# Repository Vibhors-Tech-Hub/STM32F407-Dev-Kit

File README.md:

# Tiny, yet powerful

The PCB for this project is just **66*59.5mm**, which is not exactly tiny, but still has features that go beyond it's  size. It packs a STM32F407, debugger (STM32F103), Ethernet, a powerful motor driver, 24-bit ADC configured for a 4 - wire Kelvin load, DAC and mic into this tiny footprint.

# Why did I build this?

I had designed general dev boards for the ESP32, or the RP2040, but never worked with the STM32 family before. And I also wanted to make a really complex PCB to brush up my skills, so I decided on this.

# Double-sided component placement

While I was designing this PCB, I realised that in real-life applications, size is a key deciding factor; something I had never taken very seriously. So, I challenged to make this board under 70*70mm this time. Due to which, I had to place **components on both sides**. Not only does it make the PCB smaller, but also improves SI and clears up board space.

# 4-layer design

A 2-layer design was clearly not an option here. I both analog and digital circuitry here, requiring clear return paths. So, I decided on a 4 layer board with a GND and power plane. The power plane is sectioned into 12V and 3V3 volts. I did this because while most of the PCB needed 3.3V, the motor driver required +12V with minimal voltage drops and maximum current. But when only a few tracks were left, I couldn't find space on the outer two signal layers. I only had two options from there; either upgrade to a 6 layer board (expensive and really time consuming), or use a power plane for a few signals. I thought it might ruin the return paths for sensitive signals, so I googled for guides on that topic. After going through the ["Should You Route Signals in Your PCB Power Plane?" by Altium Academy](https://resources.altium.com/p/should-you-route-signals-your-pcb-power-plane), I decided to use the Vcc power plane for routing leftover signals.

# GPIO headers

To keep the form factor of the PCB low and keep things organised, I didn't breakout GPIO headers. Although this limits the capabilities of the controller to the existing peripherals only, I still went with it as the whole idea of this project was to design a compact, complex PCB for learning new things. To expand the functionality a bit, I exposed two headers for UART and CAN.
# Motor drivers

In the beginning, I planned on two motor drivers, as in the Block Diagram and Power budget. But while designing the schematic, I thought that a single driver was enough and didn't design the second. But to keep things upgradeable, I still kept it in the Power budget and block diagram

# Power Supply

The board requires **+12v, +3V3 and +1V8** to work. For that, I use a 3-pin 10A TBC for inputting 12V, and regulating it down to +3V3 and +1V8. As calculated in the power budget, I need a power supply capable of delivering roughly 10A, though with the second motor removed, a 7.5A supply may also be used.

# How to use it?

1) Solder your PCB
2) Use an **ST-Link debugger (recommended)/USB to UARTconverter** to flash the [**DAPLink firmware by ARMbed**](https://github.com/ARMmbed/DAPLink) onto the STM32F103
3) Plug it in, and you're ready to go!

# Block Diagram

# PCB

# 3D view (front)

# 3D view (back)

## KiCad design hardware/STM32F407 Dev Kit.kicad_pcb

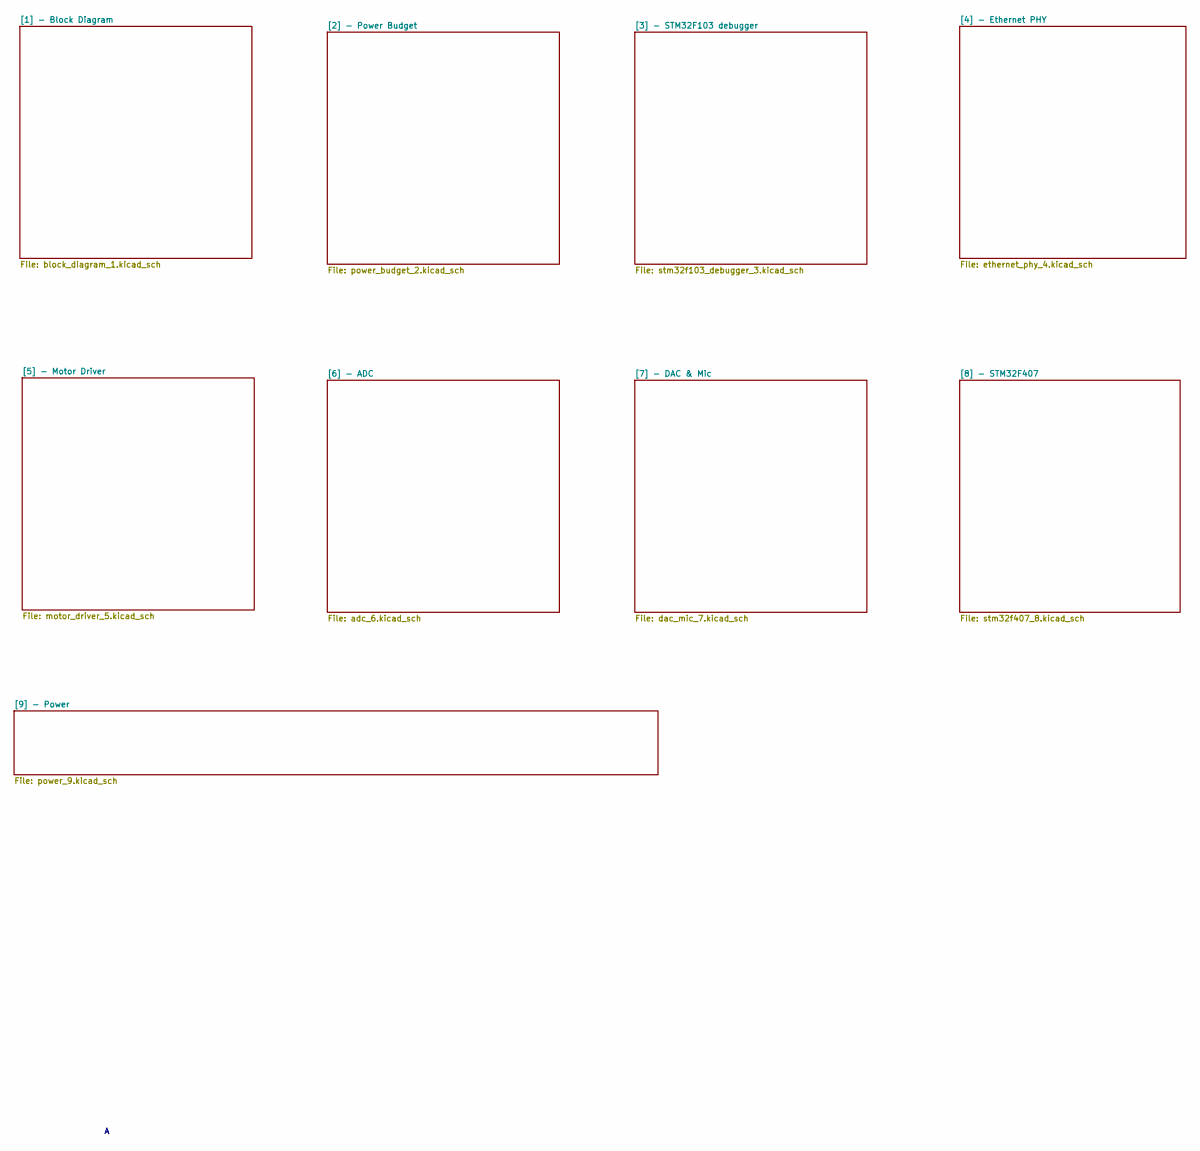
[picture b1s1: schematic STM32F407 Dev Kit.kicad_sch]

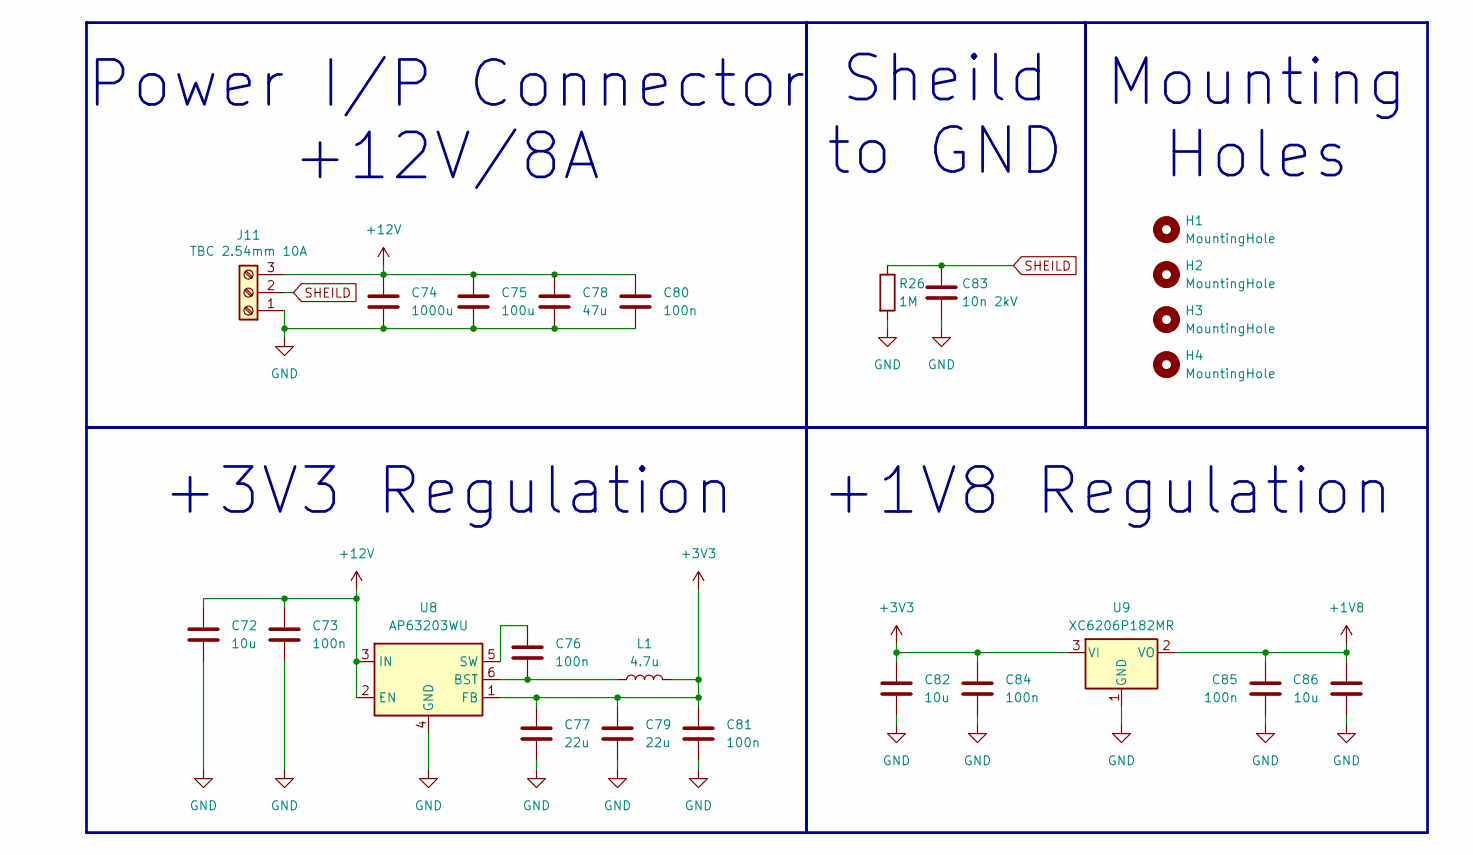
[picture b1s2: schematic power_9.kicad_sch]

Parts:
C72, C82, C86: 10u; C_0805_2012Metric_Pad1.18x1.45mm_HandSolder
C73, C76, C80, C81, C84, C85: 100n; C_0805_2012Metric_Pad1.18x1.45mm_HandSolder
C74: 1000u; CP_Elec_10x12.5
C75: 100u; C_1210_3225Metric_Pad1.33x2.70mm_HandSolder
C77, C79: 22u; C_0805_2012Metric_Pad1.18x1.45mm_HandSolder
C78: 47u; C_0805_2012Metric_Pad1.18x1.45mm_HandSolder
C83: 10n 2kV; C_1812_4532Metric_Pad1.57x3.40mm_HandSolder
H1, H2, H3, H4: MountingHole; MountingHole_3.5mm
J11: TBC 2.54mm 10A; TerminalBlock_Xinya_XY308-2.54-3P_1x03_P2.54mm_Horizontal
L1: 4.7u; L_0805_2012Metric_Pad1.05x1.20mm_HandSolder
R26: 1M; R_0805_2012Metric_Pad1.20x1.40mm_HandSolder
U8: AP63203WU; TSOT-23-6_HandSoldering
U9: XC6206P182MR; SOT-23-3

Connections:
+1V8: C85.1, C86.1, U9.2 (VO); also elsewhere on the board
+3V3: C77.1, C79.1, C81.1, C82.1, C84.1, L1.2, U8.1 (FB), U9.3 (VI); also elsewhere on the board
+12V: C72.1, C73.1, C74.1, C75.1, C78.1, C80.1, J11.3, U8.2 (EN), U8.3 (IN); also elsewhere on the board
GND: C72.2, C73.2, C74.2, C75.2, C77.2, C78.2, C79.2, C80.2, C81.2, C82.2, C83.2, C84.2, C85.2, C86.2, J11.1, R26.2, U8.4 (GND), U9.1 (GND); also elsewhere on the board
unnamed: C76.2, L1.1, U8.6 (BST)
unnamed: C76.1, U8.5 (SW)
SHEILD: C83.1, J11.2, R26.1; also elsewhere on the board

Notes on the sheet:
+3V3 Regulation
Sheild to GND
Power I/P Connector +12V/8A
Mounting Holes
+1V8 Regulation

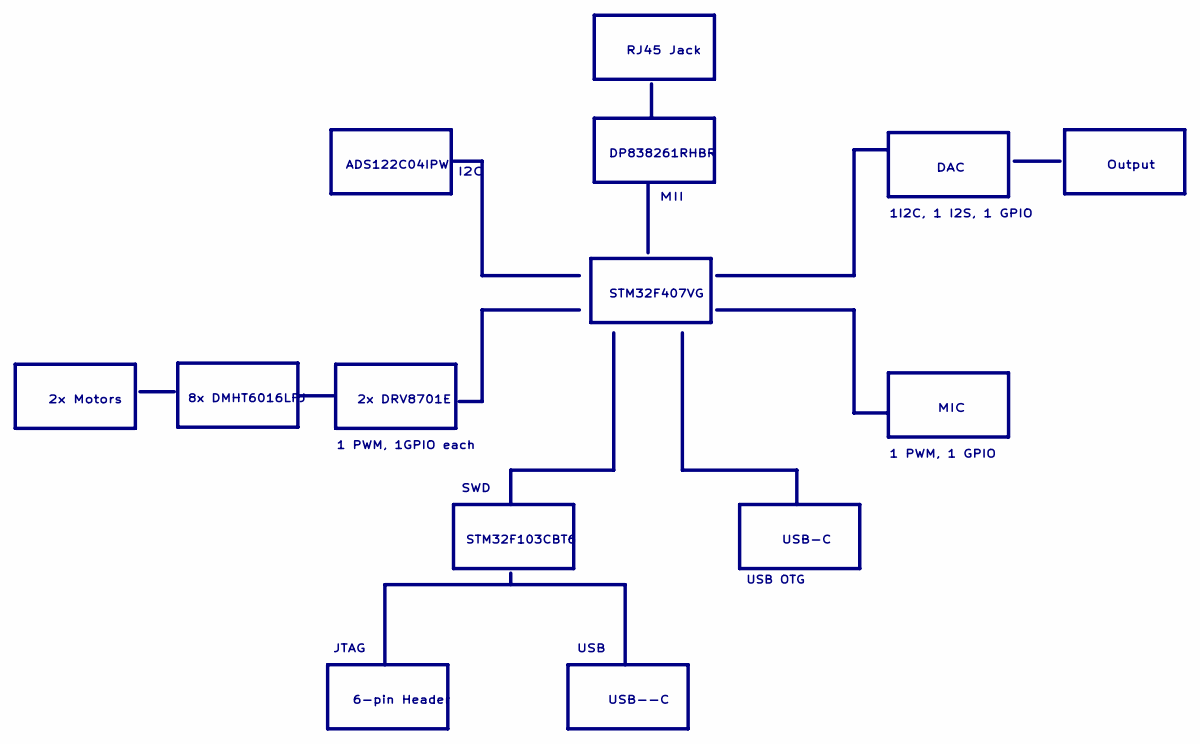
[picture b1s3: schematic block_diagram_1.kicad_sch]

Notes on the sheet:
6-pin Header
JTAG
DP838261RHBR
ADS122C04IPW
USB--C
2x Motors
USB-C
STM32F103CBT6
1 PWM, 1GPIO each
8x DMHT6016LFJ
STM32F407VG
SWD
Output
MIC
DAC
2x DRV8701E
RJ45 Jack
I2C
1I2C, 1 I2S, 1 GPIO
1 PWM, 1 GPIO
MII
USB
USB OTG

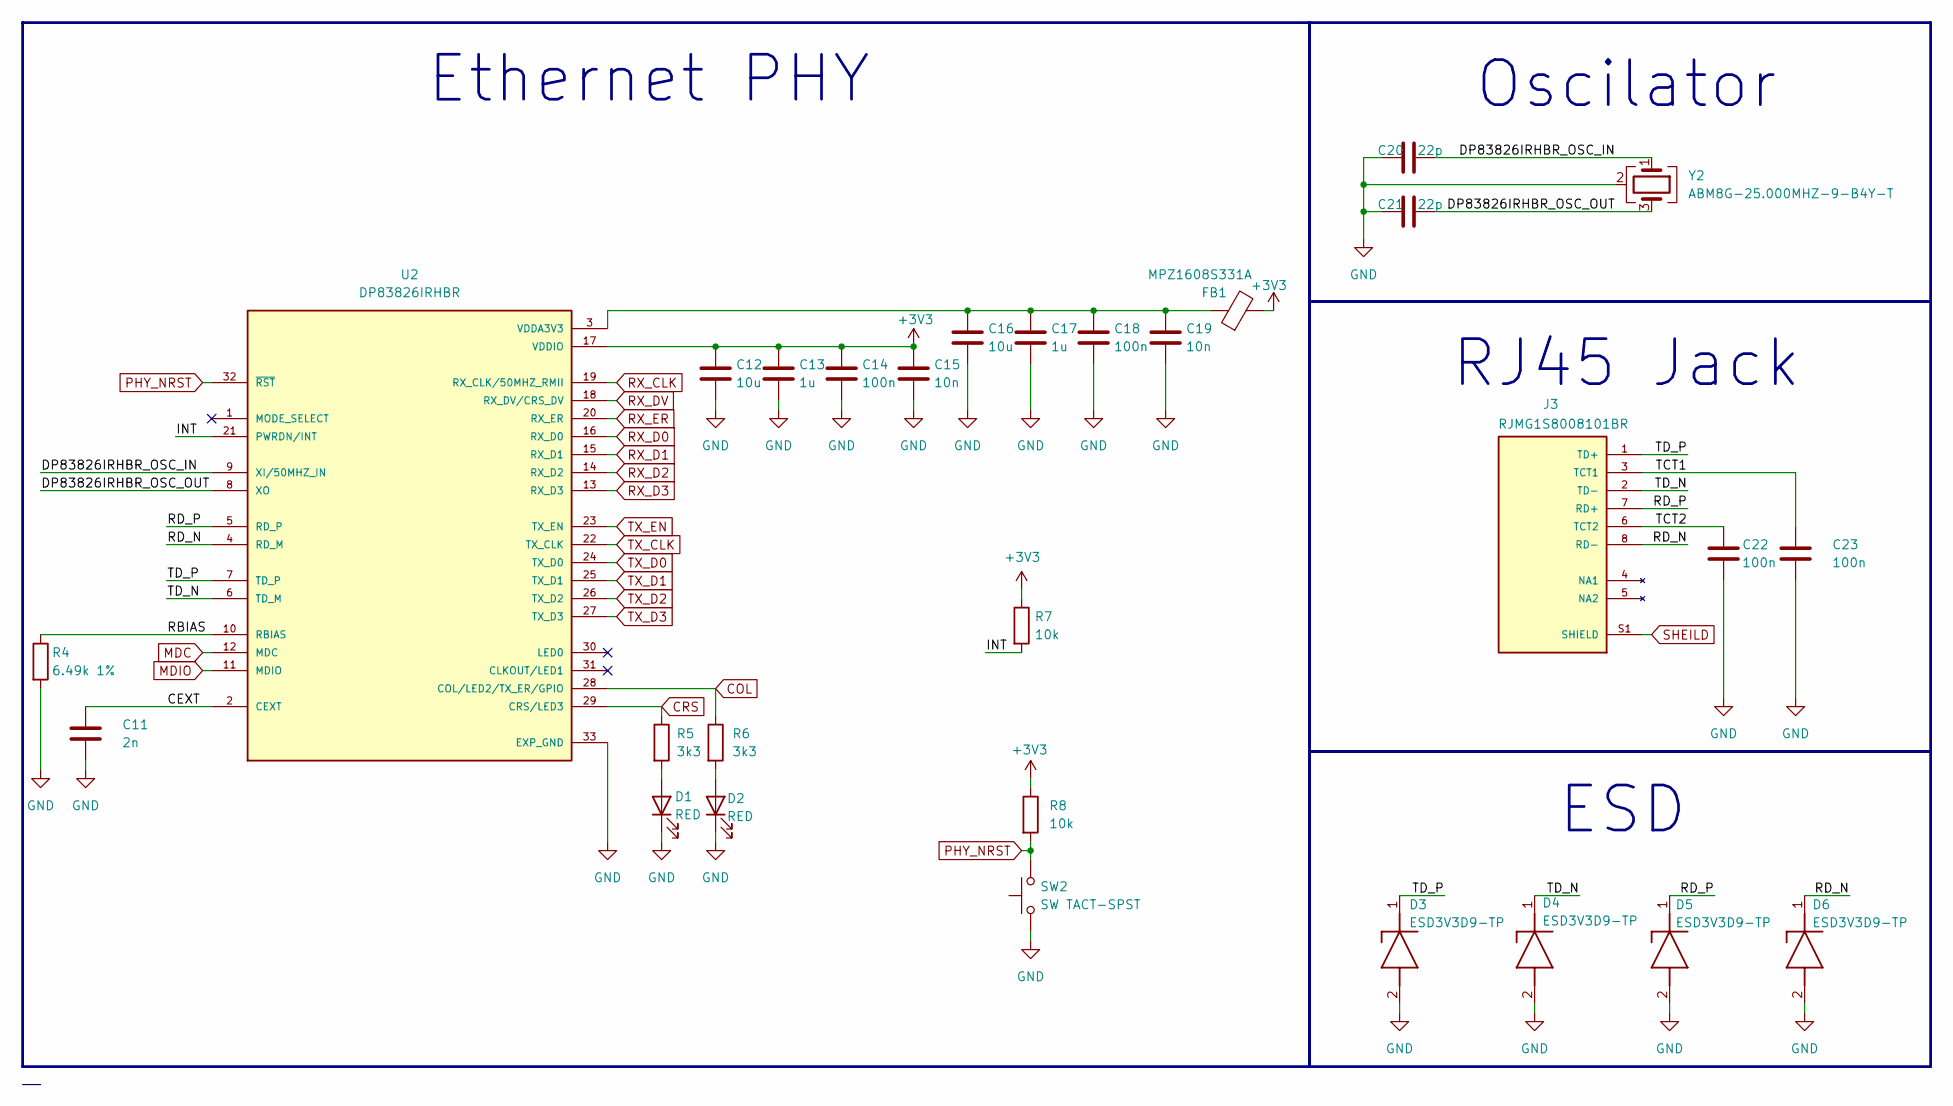
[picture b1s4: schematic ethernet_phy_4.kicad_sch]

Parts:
C11: 2n; C_0805_2012Metric_Pad1.18x1.45mm_HandSolder
C12, C16: 10u; C_0805_2012Metric_Pad1.18x1.45mm_HandSolder
C13, C17: 1u; C_0805_2012Metric_Pad1.18x1.45mm_HandSolder
C14, C18, C22, C23: 100n; C_0805_2012Metric_Pad1.18x1.45mm_HandSolder
C15, C19: 10n; C_0805_2012Metric_Pad1.18x1.45mm_HandSolder
C20, C21: 22p; C_0805_2012Metric_Pad1.18x1.45mm_HandSolder
D1, D2: RED; LED_0805_2012Metric_Pad1.15x1.40mm_HandSolder
D3, D4, D5, D6: ESD3V3D9-TP; D_SOD-923; Manufacturer_Part_Number ESD3V3D9-TP; Mouser Part Number 833-ESD3V3D9-TP
FB1: MPZ1608S331A; C_0603_1608Metric_Pad1.08x0.95mm_HandSolder
J3: RJMG1S8008101BR; PARTREV A
R4: 6.49k 1%; R_0805_2012Metric_Pad1.20x1.40mm_HandSolder
R5, R6: 3k3; R_0805_2012Metric_Pad1.20x1.40mm_HandSolder
R7, R8: 10k; R_0805_2012Metric_Pad1.20x1.40mm_HandSolder
SW2: SW TACT-SPST; SW_Push_SPST_NO_Alps_SKRK
U2: DP83826IRHBR; PARTREV G
Y2: ABM8G-25.000MHZ-9-B4Y-T; Crystal_SMD_3225-4Pin_3.2x2.5mm_HandSoldering

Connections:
+3V3: C12.1, C13.1, C14.1, C15.1, FB1.2, R7.1, R8.1, U2.17 (VDDIO); also elsewhere on the board
/[4] - Ethernet PHY/CEXT: C11.1, U2.2 (CEXT)
/[4] - Ethernet PHY/DP83826IRHBR_OSC_IN: C20.2, U2.9 (XI/50MHZ_IN), Y2.1
/[4] - Ethernet PHY/DP83826IRHBR_OSC_OUT: C21.2, U2.8 (XO), Y2.3
/[4] - Ethernet PHY/INT: R7.2, U2.21 (PWRDN/INT)
/[4] - Ethernet PHY/RBIAS: R4.1, U2.10 (RBIAS)
/[4] - Ethernet PHY/RD_N: D6.1 (K), J3.8 (RD-), U2.4 (RD_M)
/[4] - Ethernet PHY/RD_P: D5.1 (K), J3.7 (RD+), U2.5 (RD_P)
/[4] - Ethernet PHY/TCT1: C23.1, J3.3 (TCT1)
/[4] - Ethernet PHY/TCT2: C22.1, J3.6 (TCT2)
/[4] - Ethernet PHY/TD_N: D4.1 (K), J3.2 (TD-), U2.6 (TD_M)
/[4] - Ethernet PHY/TD_P: D3.1 (K), J3.1 (TD+), U2.7 (TD_P)
COL: R6.1, U2.28 (COL/LED2/TX_ER/GPIO); also elsewhere on the board
CRS: R5.1, U2.29 (CRS/LED3); also elsewhere on the board
GND: C11.2, C12.2, C13.2, C14.2, C15.2, C16.2, C17.2, C18.2, C19.2, C20.1, C21.1, C22.2, C23.2, D1.1 (K), D2.1 (K), D3.2 (A), D4.2 (A), D5.2 (A), D6.2 (A), R4.2, SW2.1, U2.33 (EXP_GND), Y2.2 (G), Y2.4 (G); also elsewhere on the board
MDC: U2.12 (MDC); also elsewhere on the board
MDIO: U2.11 (MDIO); also elsewhere on the board
unnamed: D1.2 (A), R5.2
unnamed: D2.2 (A), R6.2
unnamed: C16.1, C17.1, C18.1, C19.1, FB1.1, U2.3 (VDDA3V3)
PHY_NRST: R8.2, SW2.2, U2.32 (~RST); also elsewhere on the board
RX_CLK: U2.19 (RX_CLK/50MHZ_RMII); also elsewhere on the board
RX_D0: U2.16 (RX_D0); also elsewhere on the board
RX_D1: U2.15 (RX_D1); also elsewhere on the board
RX_D2: U2.14 (RX_D2); also elsewhere on the board
RX_D3: U2.13 (RX_D3); also elsewhere on the board
RX_DV: U2.18 (RX_DV/CRS_DV); also elsewhere on the board
RX_ER: U2.20 (RX_ER); also elsewhere on the board
SHEILD: J3.S1 (SHIELD), J3.S2 (SHIELD); also elsewhere on the board
TX_CLK: U2.22 (TX_CLK); also elsewhere on the board
TX_D0: U2.24 (TX_D0); also elsewhere on the board
TX_D1: U2.25 (TX_D1); also elsewhere on the board
TX_D2: U2.26 (TX_D2); also elsewhere on the board
TX_D3: U2.27 (TX_D3); also elsewhere on the board
TX_EN: U2.23 (TX_EN); also elsewhere on the board

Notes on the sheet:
ESD
RJ45 Jack
Ethernet PHY
Oscilator

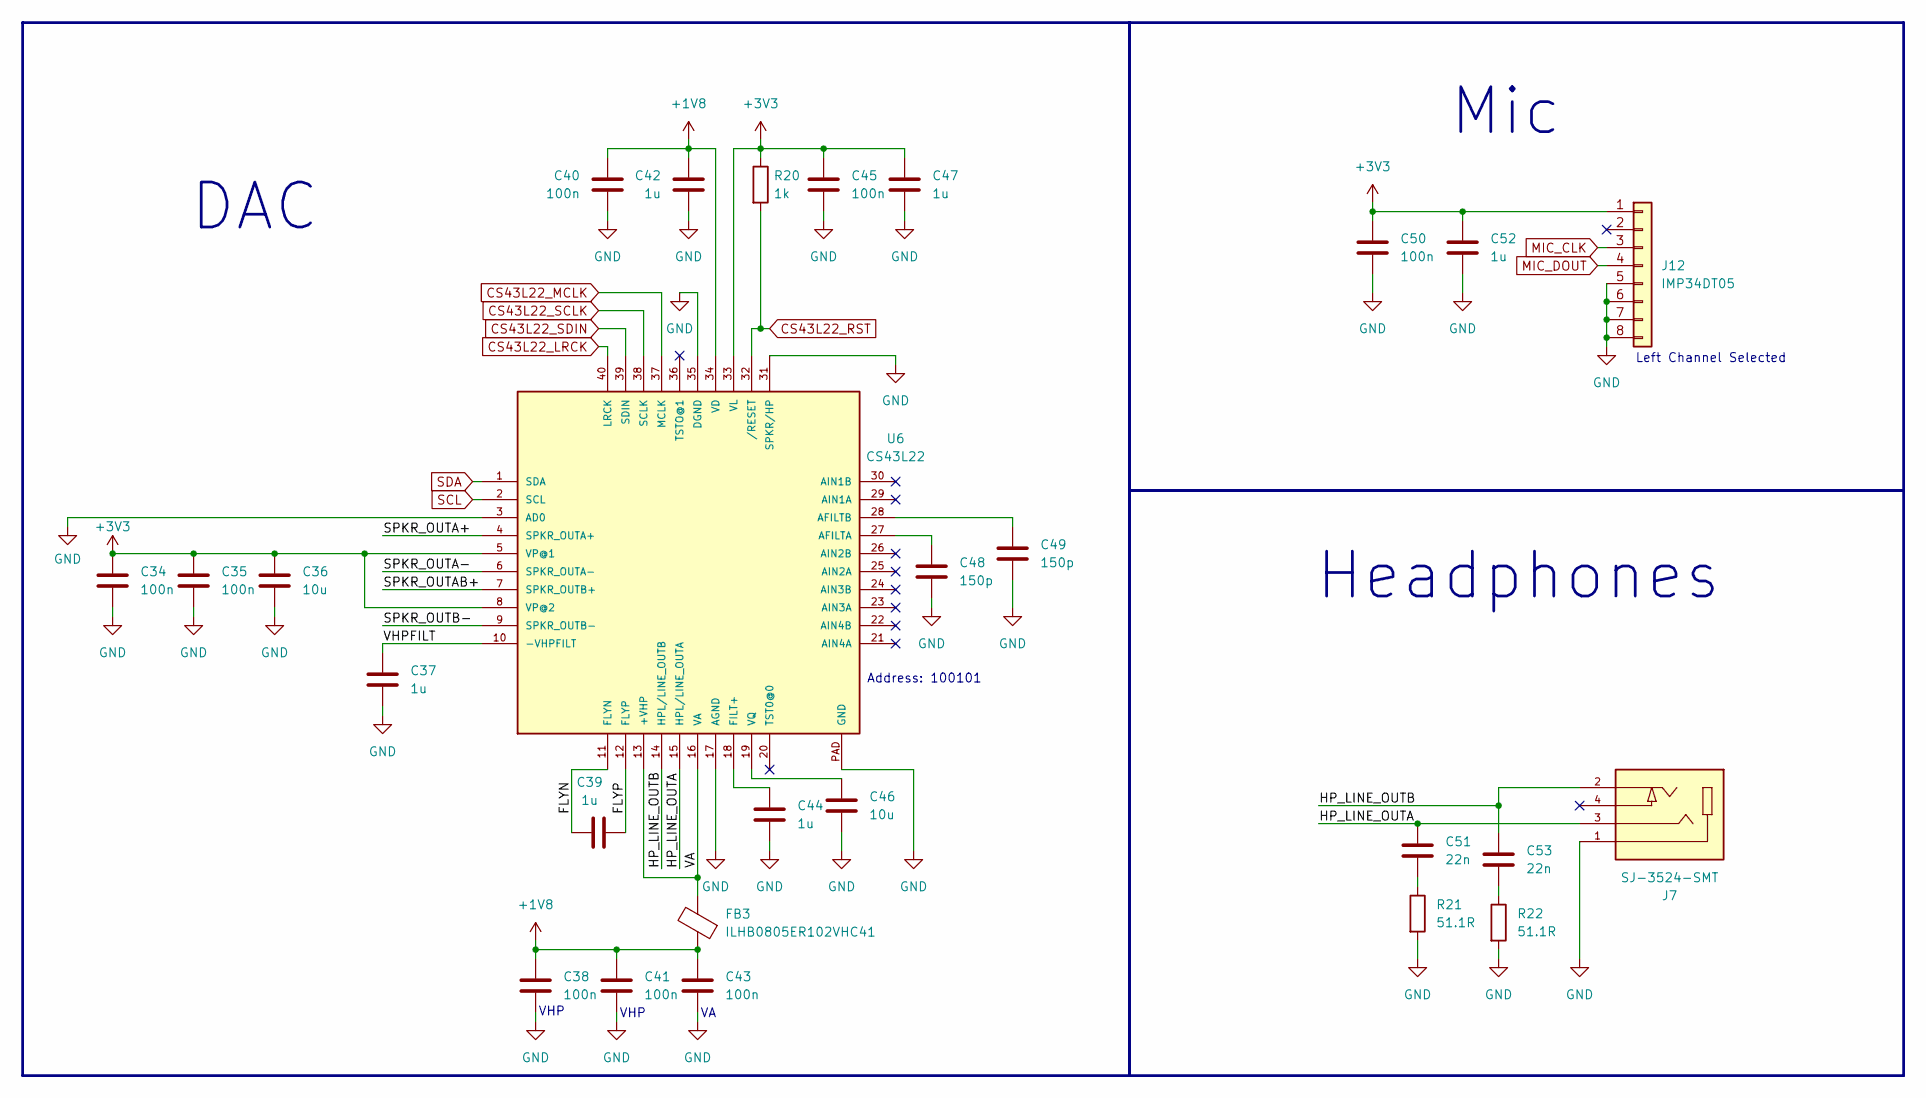
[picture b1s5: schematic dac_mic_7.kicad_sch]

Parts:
C34, C35, C38, C40, C41, C43, C45, C50: 100n; C_0805_2012Metric_Pad1.18x1.45mm_HandSolder
C36, C46: 10u; C_0805_2012Metric_Pad1.18x1.45mm_HandSolder
C37, C39, C42, C44, C47, C52: 1u; C_0805_2012Metric_Pad1.18x1.45mm_HandSolder
C48, C49: 150p; C_0805_2012Metric_Pad1.18x1.45mm_HandSolder
C51, C53: 22n; C_0805_2012Metric_Pad1.18x1.45mm_HandSolder
FB3: ILHB0805ER102VHC41; C_0805_2012Metric_Pad1.18x1.45mm_HandSolder
J7: SJ-3524-SMT; PARTREV 1.03
J12: IMP34DT05; IMP34DT06JTR
R20: 1k; R_0805_2012Metric_Pad1.20x1.40mm_HandSolder
R21, R22: 51.1R; R_0805_2012Metric_Pad1.20x1.40mm_HandSolder
U6: CS43L22; VQFN-40-1EP_6x6mm_P0.5mm_EP3.5x3.5mm

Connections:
+1V8: C38.2, C40.1, C41.2, C42.1, C43.2, FB3.1, U6.34 (VD); also elsewhere on the board
+3V3: C34.1, C35.1, C36.1, C45.1, C47.1, C50.1, C52.1, J12.1, R20.1, U6.5 (VP@1), U6.8 (VP@2), U6.33 (VL); also elsewhere on the board
/[7] - DAC & Mic/FLYN: C39.1, U6.11 (FLYN)
/[7] - DAC & Mic/FLYP: C39.2, U6.12 (FLYP)
/[7] - DAC & Mic/HP_LINE_OUTA: C51.2, J7.3, U6.15 (HPL/LINE_OUTA)
/[7] - DAC & Mic/HP_LINE_OUTB: C53.2, J7.2, U6.14 (HPL/LINE_OUTB)
/[7] - DAC & Mic/SPKR_OUTA+: U6.4 (SPKR_OUTA+)
/[7] - DAC & Mic/SPKR_OUTA-: U6.6 (SPKR_OUTA-)
/[7] - DAC & Mic/SPKR_OUTAB+: U6.7 (SPKR_OUTB+)
/[7] - DAC & Mic/SPKR_OUTB-: U6.9 (SPKR_OUTB-)
/[7] - DAC & Mic/VA: FB3.2, U6.13 (+VHP), U6.16 (VA)
/[7] - DAC & Mic/VHPFILT: C37.2, U6.10 (-VHPFILT)
CS43L22_LRCK: U6.40 (LRCK); also elsewhere on the board
CS43L22_MCLK: U6.37 (MCLK); also elsewhere on the board
CS43L22_RST: R20.2, U6.32 (/RESET); also elsewhere on the board
CS43L22_SCLK: U6.38 (SCLK); also elsewhere on the board
CS43L22_SDIN: U6.39 (SDIN); also elsewhere on the board
GND: C34.2, C35.2, C36.2, C37.1, C38.1, C40.2, C41.1, C42.2, C43.1, C44.2, C45.2, C46.2, C47.2, C48.2, C49.2, C50.2, C52.2, J7.1, J12.5, J12.6, J12.7, J12.8, R21.2, R22.2, U6.3 (AD0), U6.17 (AGND), U6.31 (SPKR/HP), U6.35 (DGND), U6.PAD (GND); also elsewhere on the board
MIC_CLK: J12.3; also elsewhere on the board
MIC_DOUT: J12.4; also elsewhere on the board
unnamed: C51.1, R21.1
unnamed: C53.1, R22.1
unnamed: C48.1, U6.27 (AFILTA)
unnamed: C49.1, U6.28 (AFILTB)
unnamed: C44.1, U6.18 (FILT+)
unnamed: C46.1, U6.19 (VQ)
SCL: U6.2 (SCL); also elsewhere on the board
SDA: U6.1 (SDA); also elsewhere on the board

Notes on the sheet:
Headphones
VHP
DAC
Address: 100101
Left Channel Selected
Mic

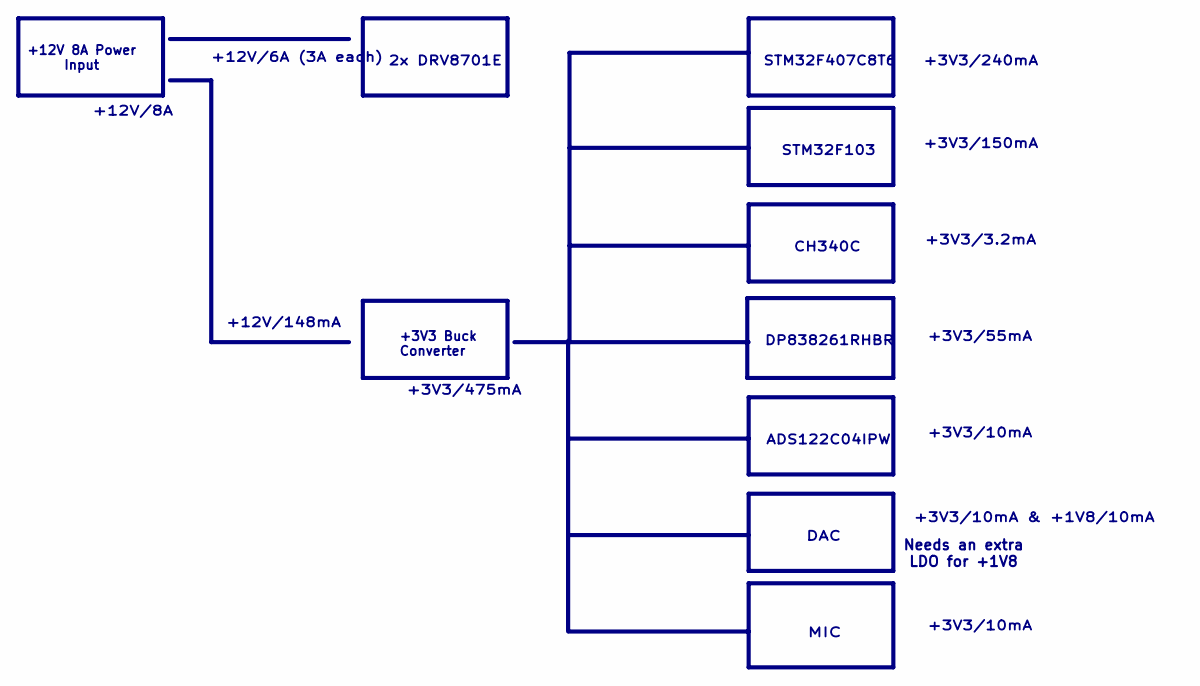
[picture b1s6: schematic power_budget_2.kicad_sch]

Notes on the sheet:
+3V3/3.2mA
DP838261RHBR
CH340C
Needs an extra LDO for +1V8
+3V3 Buck Converter
ADS122C04IPW
2x DRV8701E
+3V3/10mA
+3V3/475mA
STM32F103
+3V3/150mA
+12V/6A (3A each)
+3V3/55mA
DAC
+12V/148mA
MIC
STM32F407C8T6
+12V/8A
+3V3/240mA
+3V3/10mA & +1V8/10mA
+12V 8A Power Input

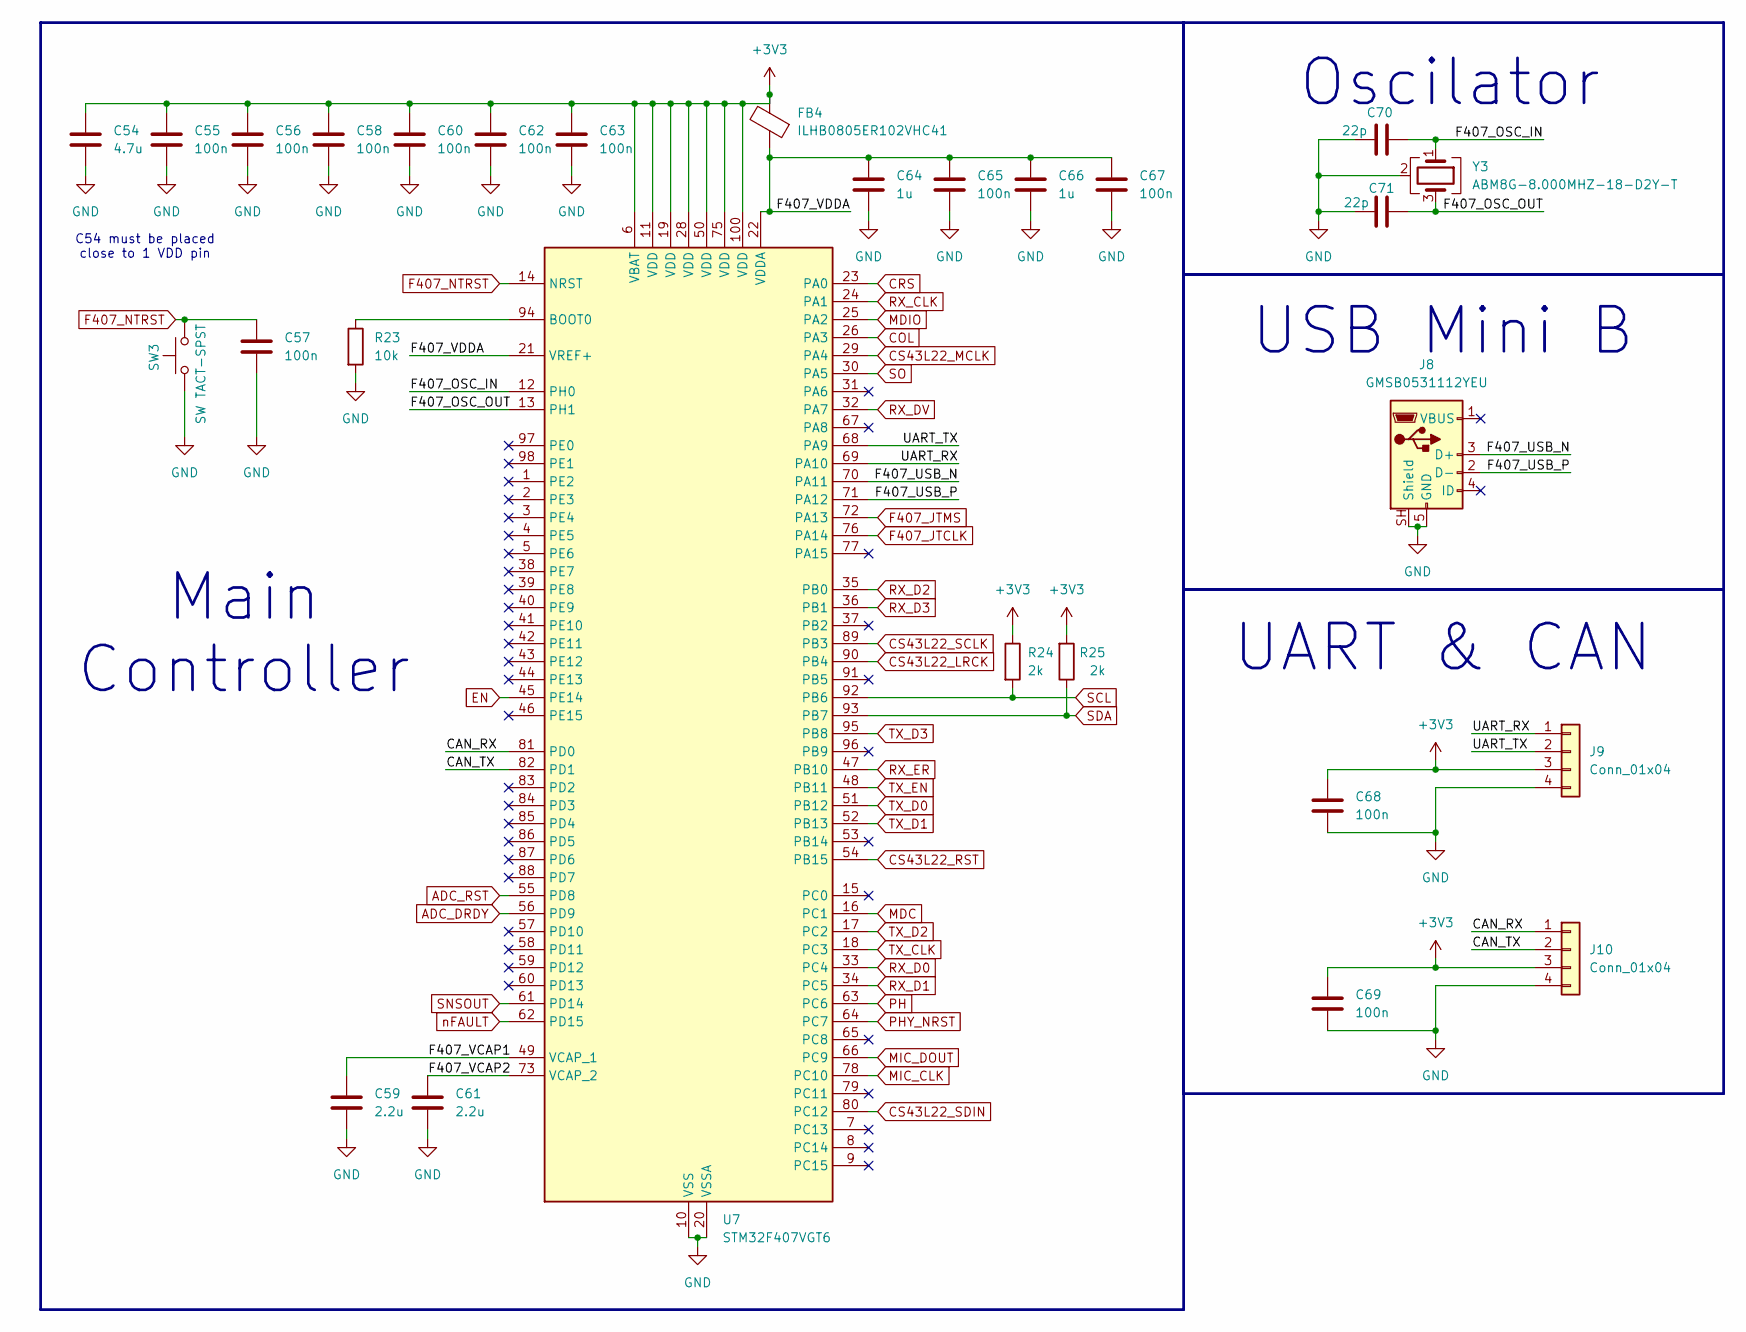
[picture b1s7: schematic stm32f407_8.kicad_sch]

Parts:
C54: 4.7u; C_0805_2012Metric_Pad1.18x1.45mm_HandSolder
C55, C56, C57, C58, C60, C62, C63, C65, C67, C68, C69: 100n; C_0805_2012Metric_Pad1.18x1.45mm_HandSolder
C59, C61: 2.2u; C_0805_2012Metric_Pad1.18x1.45mm_HandSolder
C64, C66: 1u; C_0805_2012Metric_Pad1.18x1.45mm_HandSolder
C70, C71: 22p; C_0805_2012Metric_Pad1.18x1.45mm_HandSolder
FB4: ILHB0805ER102VHC41; C_0805_2012Metric_Pad1.18x1.45mm_HandSolder
J8: GMSB0531112YEU; USB_Mini-B_Wuerth_65100516121_Horizontal
J9, J10: Conn_01x04; PinHeader_1x04_P2.54mm_Vertical
R23: 10k; R_0805_2012Metric_Pad1.20x1.40mm_HandSolder
R24, R25: 2k; R_0805_2012Metric_Pad1.20x1.40mm_HandSolder
SW3: SW TACT-SPST; SW_Push_SPST_NO_Alps_SKRK
U7: STM32F407VGT6; LQFP-100_14x14mm_P0.5mm
Y3: ABM8G-8.000MHZ-18-D2Y-T; Crystal_SMD_3225-4Pin_3.2x2.5mm_HandSoldering

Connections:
+3V3: C54.1, C55.1, C56.1, C58.1, C60.1, C62.1, C63.1, C68.1, C69.1, FB4.2, J9.3, J10.3, R24.1, R25.2, U7.6 (VBAT), U7.11 (VDD), U7.19 (VDD), U7.28 (VDD), U7.50 (VDD), U7.75 (VDD), U7.100 (VDD); also elsewhere on the board
/[8] - STM32F407/CAN_RX: J10.1, U7.81 (PD0)
/[8] - STM32F407/CAN_TX: J10.2, U7.82 (PD1)
/[8] - STM32F407/F407_OSC_IN: C70.2, U7.12 (PH0), Y3.1
/[8] - STM32F407/F407_OSC_OUT: C71.2, U7.13 (PH1), Y3.3
/[8] - STM32F407/F407_USB_N: J8.3 (D+), U7.70 (PA11)
/[8] - STM32F407/F407_USB_P: J8.2 (D-), U7.71 (PA12)
/[8] - STM32F407/F407_VCAP1: C59.1, U7.49 (VCAP_1)
/[8] - STM32F407/F407_VCAP2: C61.1, U7.73 (VCAP_2)
/[8] - STM32F407/F407_VDDA: C64.1, C65.1, C66.1, C67.1, FB4.1, U7.21 (VREF+), U7.22 (VDDA)
/[8] - STM32F407/UART_RX: J9.1, U7.69 (PA10)
/[8] - STM32F407/UART_TX: J9.2, U7.68 (PA9)
ADC_DRDY: U7.56 (PD9); also elsewhere on the board
ADC_RST: U7.55 (PD8); also elsewhere on the board
COL: U7.26 (PA3); also elsewhere on the board
CRS: U7.23 (PA0); also elsewhere on the board
CS43L22_LRCK: U7.90 (PB4); also elsewhere on the board
CS43L22_MCLK: U7.29 (PA4); also elsewhere on the board
CS43L22_RST: U7.54 (PB15); also elsewhere on the board
CS43L22_SCLK: U7.89 (PB3); also elsewhere on the board
CS43L22_SDIN: U7.80 (PC12); also elsewhere on the board
EN: U7.45 (PE14); also elsewhere on the board
F407_JTCLK: U7.76 (PA14); also elsewhere on the board
F407_JTMS: U7.72 (PA13); also elsewhere on the board
F407_NTRST: C57.1, SW3.2, U7.14 (NRST); also elsewhere on the board
GND: C54.2, C55.2, C56.2, C57.2, C58.2, C59.2, C60.2, C61.2, C62.2, C63.2, C64.2, C65.2, C66.2, C67.2, C68.2, C69.2, C70.1, C71.1, J8.5 (GND), J8.SH (Shield), J9.4, J10.4, R23.2, SW3.1, U7.10 (VSS), U7.20 (VSSA), U7.27 (VSS), U7.74 (VSS), U7.99 (VSS), Y3.2 (G), Y3.4 (G); also elsewhere on the board
MDC: U7.16 (PC1); also elsewhere on the board
MDIO: U7.25 (PA2); also elsewhere on the board
MIC_CLK: U7.78 (PC10); also elsewhere on the board
MIC_DOUT: U7.66 (PC9); also elsewhere on the board
unnamed: R23.1, U7.94 (BOOT0)
PH: U7.63 (PC6); also elsewhere on the board
PHY_NRST: U7.64 (PC7); also elsewhere on the board
RX_CLK: U7.24 (PA1); also elsewhere on the board
RX_D0: U7.33 (PC4); also elsewhere on the board
RX_D1: U7.34 (PC5); also elsewhere on the board
RX_D2: U7.35 (PB0); also elsewhere on the board
RX_D3: U7.36 (PB1); also elsewhere on the board
RX_DV: U7.32 (PA7); also elsewhere on the board
RX_ER: U7.47 (PB10); also elsewhere on the board
SCL: R24.2, U7.92 (PB6); also elsewhere on the board
SDA: R25.1, U7.93 (PB7); also elsewhere on the board
SNSOUT: U7.61 (PD14); also elsewhere on the board
SO: U7.30 (PA5); also elsewhere on the board
TX_CLK: U7.18 (PC3); also elsewhere on the board
TX_D0: U7.51 (PB12); also elsewhere on the board
TX_D1: U7.52 (PB13); also elsewhere on the board
TX_D2: U7.17 (PC2); also elsewhere on the board
TX_D3: U7.95 (PB8); also elsewhere on the board
TX_EN: U7.48 (PB11); also elsewhere on the board
nFAULT: U7.62 (PD15); also elsewhere on the board

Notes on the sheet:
USB Mini B
Main Controller
Oscilator
UART & CAN
C54 must be placed close to 1 VDD pin

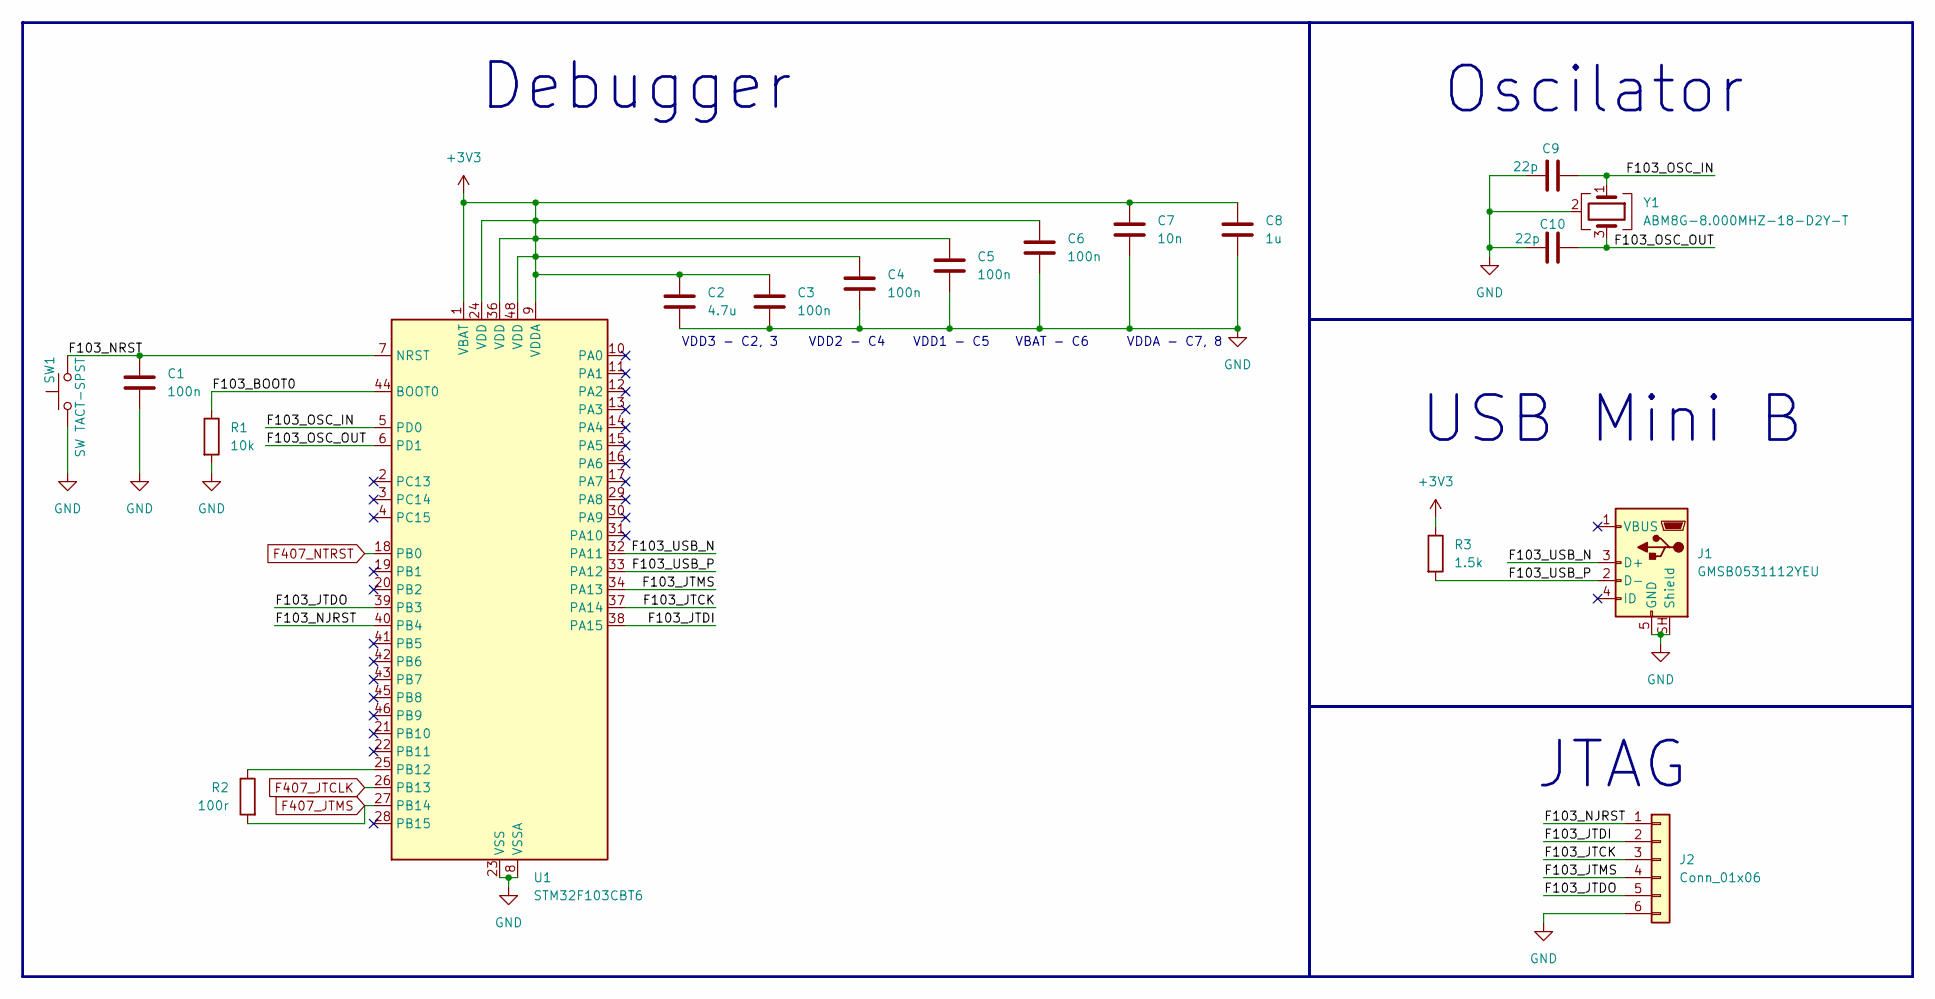
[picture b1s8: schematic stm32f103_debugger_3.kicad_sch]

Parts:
C1, C3, C4, C5, C6: 100n; C_0805_2012Metric_Pad1.18x1.45mm_HandSolder
C2: 4.7u; C_0805_2012Metric_Pad1.18x1.45mm_HandSolder
C7: 10n; C_0805_2012Metric_Pad1.18x1.45mm_HandSolder
C8: 1u; C_0805_2012Metric_Pad1.18x1.45mm_HandSolder
C9, C10: 22p; C_0805_2012Metric_Pad1.18x1.45mm_HandSolder
J1: GMSB0531112YEU; USB_Mini-B_Wuerth_65100516121_Horizontal
J2: Conn_01x06; PinHeader_1x06_P2.54mm_Vertical
R1: 10k; R_0805_2012Metric_Pad1.20x1.40mm_HandSolder
R2: 100r; R_0805_2012Metric_Pad1.20x1.40mm_HandSolder
R3: 1.5k; R_0805_2012Metric_Pad1.20x1.40mm_HandSolder
SW1: SW TACT-SPST; SW_Push_SPST_NO_Alps_SKRK
U1: STM32F103CBT6; LQFP-48_7x7mm_P0.5mm
Y1: ABM8G-8.000MHZ-18-D2Y-T; Crystal_SMD_3225-4Pin_3.2x2.5mm_HandSoldering

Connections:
+3V3: C2.1, C3.1, C4.1, C5.1, C6.1, C7.1, C8.1, R3.1, U1.1 (VBAT), U1.9 (VDDA), U1.24 (VDD), U1.36 (VDD), U1.48 (VDD); also elsewhere on the board
/[3] - STM32F103 debugger/F103_BOOT0: R1.1, U1.44 (BOOT0)
/[3] - STM32F103 debugger/F103_JTCK: J2.3, U1.37 (PA14)
/[3] - STM32F103 debugger/F103_JTDI: J2.2, U1.38 (PA15)
/[3] - STM32F103 debugger/F103_JTDO: J2.5, U1.39 (PB3)
/[3] - STM32F103 debugger/F103_JTMS: J2.4, U1.34 (PA13)
/[3] - STM32F103 debugger/F103_NJRST: J2.1, U1.40 (PB4)
/[3] - STM32F103 debugger/F103_NRST: C1.1, SW1.2, U1.7 (NRST)
/[3] - STM32F103 debugger/F103_OSC_IN: C9.2, U1.5 (PD0), Y1.1
/[3] - STM32F103 debugger/F103_OSC_OUT: C10.2, U1.6 (PD1), Y1.3
/[3] - STM32F103 debugger/F103_USB_N: J1.3 (D+), U1.32 (PA11)
/[3] - STM32F103 debugger/F103_USB_P: J1.2 (D-), R3.2, U1.33 (PA12)
F407_JTCLK: U1.26 (PB13); also elsewhere on the board
F407_JTMS: R2.2, U1.27 (PB14); also elsewhere on the board
F407_NTRST: U1.18 (PB0); also elsewhere on the board
GND: C1.2, C2.2, C3.2, C4.2, C5.2, C6.2, C7.2, C8.2, C9.1, C10.1, J1.5 (GND), J1.SH (Shield), J2.6, R1.2, SW1.1, U1.8 (VSSA), U1.23 (VSS), U1.35 (VSS), U1.47 (VSS), Y1.2 (G), Y1.4 (G); also elsewhere on the board
unnamed: R2.1, U1.25 (PB12)

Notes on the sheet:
VDDA - C7, 8
JTAG
VDD3 - C2, 3
VBAT - C6
VDD1 - C5
VDD2 - C4
Oscilator
USB Mini B
Debugger

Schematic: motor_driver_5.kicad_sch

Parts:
C24, C26: 100n; C_0805_2012Metric_Pad1.18x1.45mm_HandSolder
C25: 1u; C_0805_2012Metric_Pad1.18x1.45mm_HandSolder
C27: 100u; C_1210_3225Metric_Pad1.33x2.70mm_HandSolder
J4: B2B-XH-A(LF)(SN); JST_XH_B2B-XH-A_1x02_P2.50mm_Vertical
R9, R10, R14, R15: 10k; R_0805_2012Metric_Pad1.20x1.40mm_HandSolder
R11: 2k; R_0805_2012Metric_Pad1.20x1.40mm_HandSolder
R12: 3.3k; R_0805_2012Metric_Pad1.20x1.40mm_HandSolder
R13: 33k; R_0805_2012Metric_Pad1.20x1.40mm_HandSolder
R16: 50m; R_0805_2012Metric_Pad1.20x1.40mm_HandSolder
U3: DRV8701ERGET; QFN-24-1EP_4x4mm_P0.5mm_EP2.7x2.7mm; PARTREV B
U4: DMHT6016LFJ-13; V-DFN5045-12; PARTREV 2-2

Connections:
+3V3: R9.1; also elsewhere on the board
+12V: C25.1, C26.1, C27.1, U3.1 (VM), U4.2, U4.11, U4.13; also elsewhere on the board
/[5] - Motor Driver/CPH: C24.1, U3.3 (CPH)
/[5] - Motor Driver/CPL: C24.2, U3.4 (CPL)
/[5] - Motor Driver/GH1: U3.17 (GH1), U4.1
/[5] - Motor Driver/GH2: U3.24 (GH2), U4.12
/[5] - Motor Driver/GL1: U3.19 (GL1), U4.4
/[5] - Motor Driver/GL2: U3.22 (GL2), U4.9
/[5] - Motor Driver/IDRIVE: R13.1, U3.12 (IDRIVE)
/[5] - Motor Driver/SH1: J4.1, U3.18 (SH1), U4.3, U4.14
/[5] - Motor Driver/SH2: J4.2, U3.23 (SH2), U4.10, U4.15
/[5] - Motor Driver/SP: R16.1, U3.21 (SP), U4.5, U4.6, U4.7, U4.8
/[5] - Motor Driver/VCP: C25.2, U3.2 (VCP)
/[5] - Motor Driver/VREF: R11.2, R12.1, U3.6 (VREF)
AVDD: R11.1, R14.1, R15.1, U3.7 (AVDD)
DVDD: U3.8 (DVDD)
EN: R10.1, U3.14 (EN); also elsewhere on the board
GND: C26.2, C27.2, R10.2, R12.2, R13.2, R16.2, U3.5 (GND), U3.16 (GND), U3.20 (SN), U3.25 (GND); also elsewhere on the board
PH: U3.15 (PH); also elsewhere on the board
SNSOUT: R15.2, U3.10 (SNSOUT); also elsewhere on the board
SO: U3.11 (SO); also elsewhere on the board
nFAULT: R14.2, U3.9 (~FAULT); also elsewhere on the board
nSLEEP: R9.2, U3.13 (~SLEEP)

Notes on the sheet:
Driver
MOSFET
Connector
